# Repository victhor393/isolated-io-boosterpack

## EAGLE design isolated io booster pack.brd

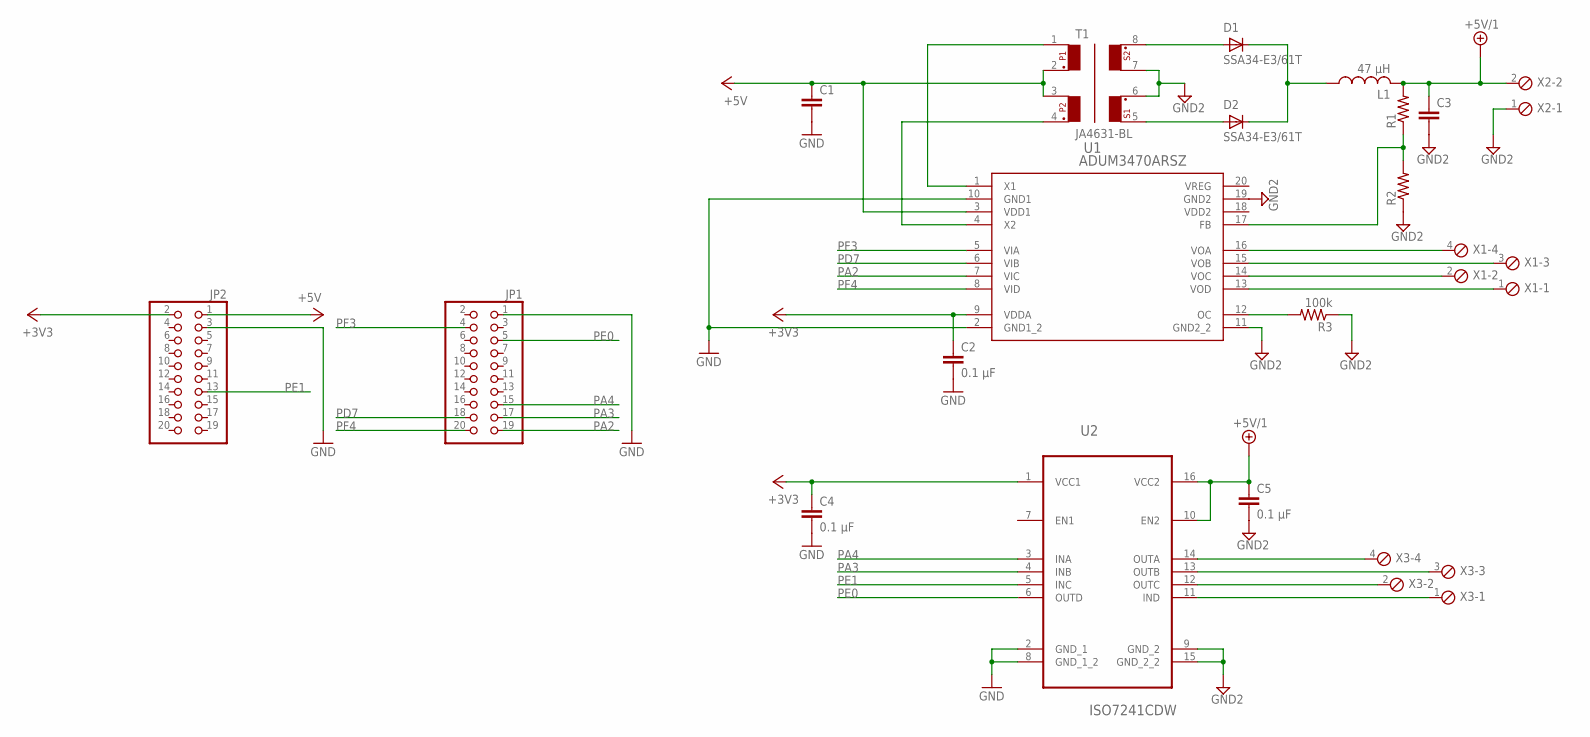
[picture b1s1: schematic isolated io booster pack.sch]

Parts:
C1, C3: C-EUC1210; C1210
C2, C4, C5: 0.1 µF; C0805
D1, D2: SSA34-E3/61T; SMA-DO214AC
JP1, JP2: PINHD-2X10; 2X10
L1: 47 µH; LPS5030
R1, R2: R-US_R0805; R0805
R3: 100k; R0805
T1: JA4631-BL
U1: ADUM3470ARSZ; RS_20
U2: ISO7241CDW; SOIC127P1030X265-16N
X1, X3: MPT4; 4POL254
X2: MPT2; 2POL254

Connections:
+3V3: C2.1, C4.1, JP2.2, U1.9 (VDDA), U2.1 (VCC1)
+5V: C1.1, JP2.1, T1.2, T1.3, U1.3 (VDD1)
+5V/1: C3.1, C5.1, L1.2, R1.2, U2.10 (EN2), U2.16 (VCC2), X2.2
GND: C1.2, C2.2, C4.2, JP1.1, JP2.3, U1.2 (GND1_2), U1.10 (GND1), U2.2 (GND_1), U2.8 (GND_1_2)
GND2: C3.2, C5.2, R2.1, R3.1, T1.6, T1.7, U1.11 (GND2_2), U1.19 (GND2), U2.9 (GND_2), U2.15 (GND_2_2), X2.1
unnamed: U1.16 (VOA), X1.4
unnamed: D1.A, T1.8
unnamed: T1.1, U1.1 (X1)
unnamed: T1.4, U1.4 (X2)
unnamed: D2.A, T1.5
unnamed: D1.K (C), D2.K (C), L1.1
unnamed: U1.15 (VOB), X1.3
unnamed: U1.14 (VOC), X1.2
unnamed: U1.13 (VOD), X1.1
unnamed: U2.14 (OUTA), X3.4
unnamed: U2.13 (OUTB), X3.3
unnamed: U2.12 (OUTC), X3.2
unnamed: U2.11 (IND), X3.1
unnamed: R1.1, R2.2, U1.17 (FB)
unnamed: R3.2, U1.12 (OC)
PA2: JP1.19, U1.7 (VIC)
PA3: JP1.17, U2.4 (INB)
PA4: JP1.15, U2.3 (INA)
PD7: JP1.18, U1.6 (VIB)
PE0: JP1.5, U2.6 (OUTD)
PE1: JP2.13, U2.5 (INC)
PF3: JP1.4, U1.5 (VIA)
PF4: JP1.20, U1.8 (VID)

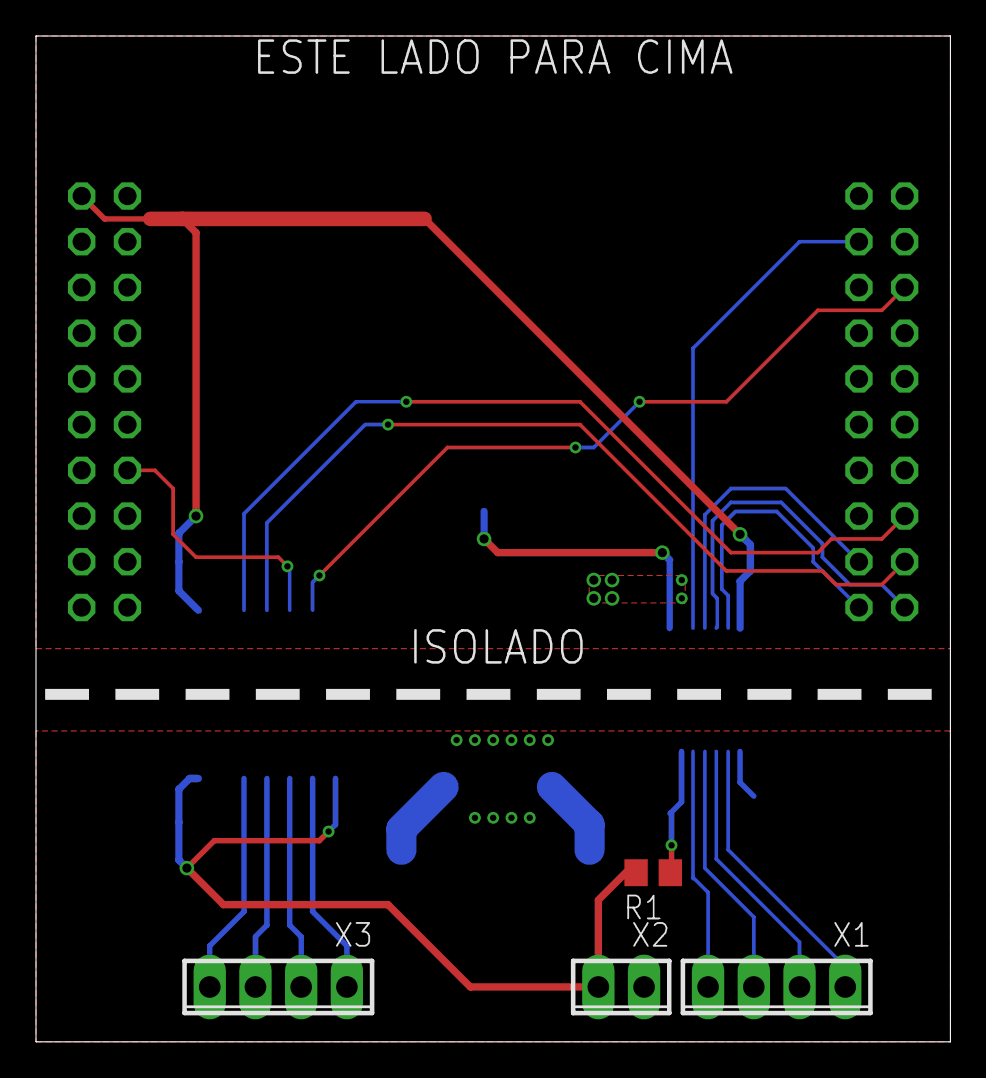
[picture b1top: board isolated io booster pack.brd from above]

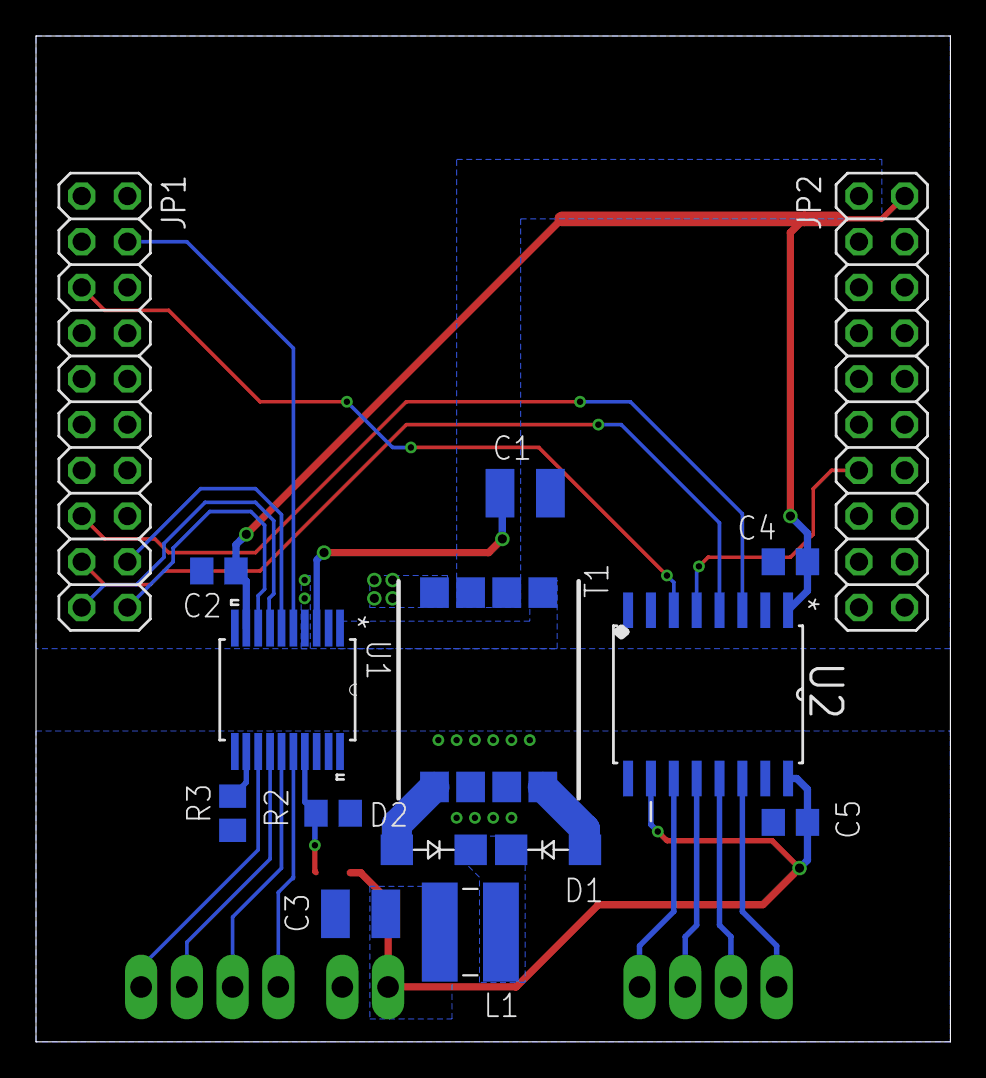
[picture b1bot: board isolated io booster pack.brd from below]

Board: 2 copper layers, 50.8 x 55.9 mm, 19 parts (15 on the bottom side), 28 nets.

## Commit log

2019-05-21 Added schematic and board layout in pdf format
